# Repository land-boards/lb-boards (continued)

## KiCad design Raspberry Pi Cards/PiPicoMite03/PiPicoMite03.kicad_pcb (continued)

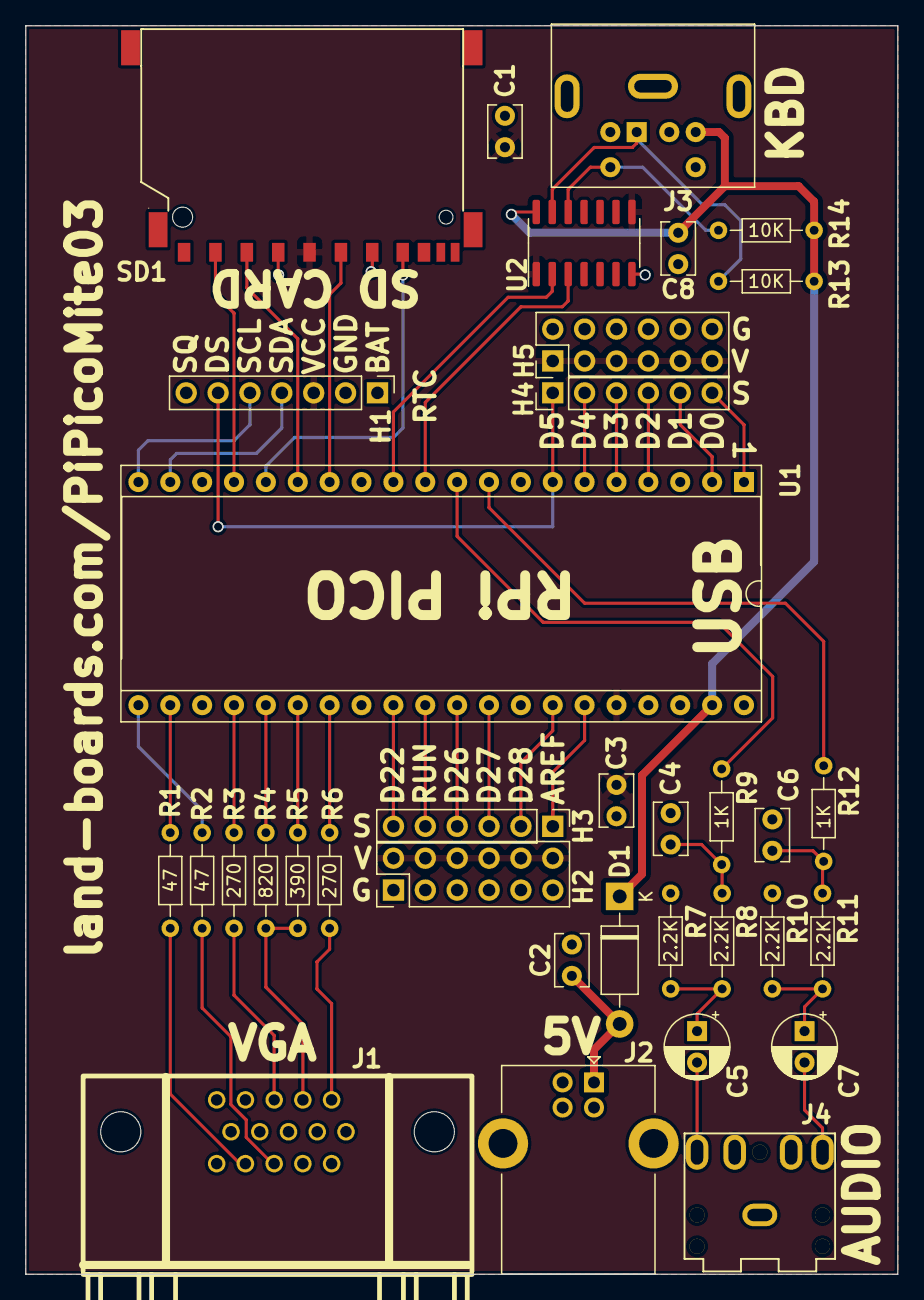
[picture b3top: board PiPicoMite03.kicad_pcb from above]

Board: 2 copper layers, 69.5 x 99.5 mm, 36 parts (0 on the bottom side), 45 nets.

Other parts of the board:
TEST: COUPON; TEST_BLK-REAR

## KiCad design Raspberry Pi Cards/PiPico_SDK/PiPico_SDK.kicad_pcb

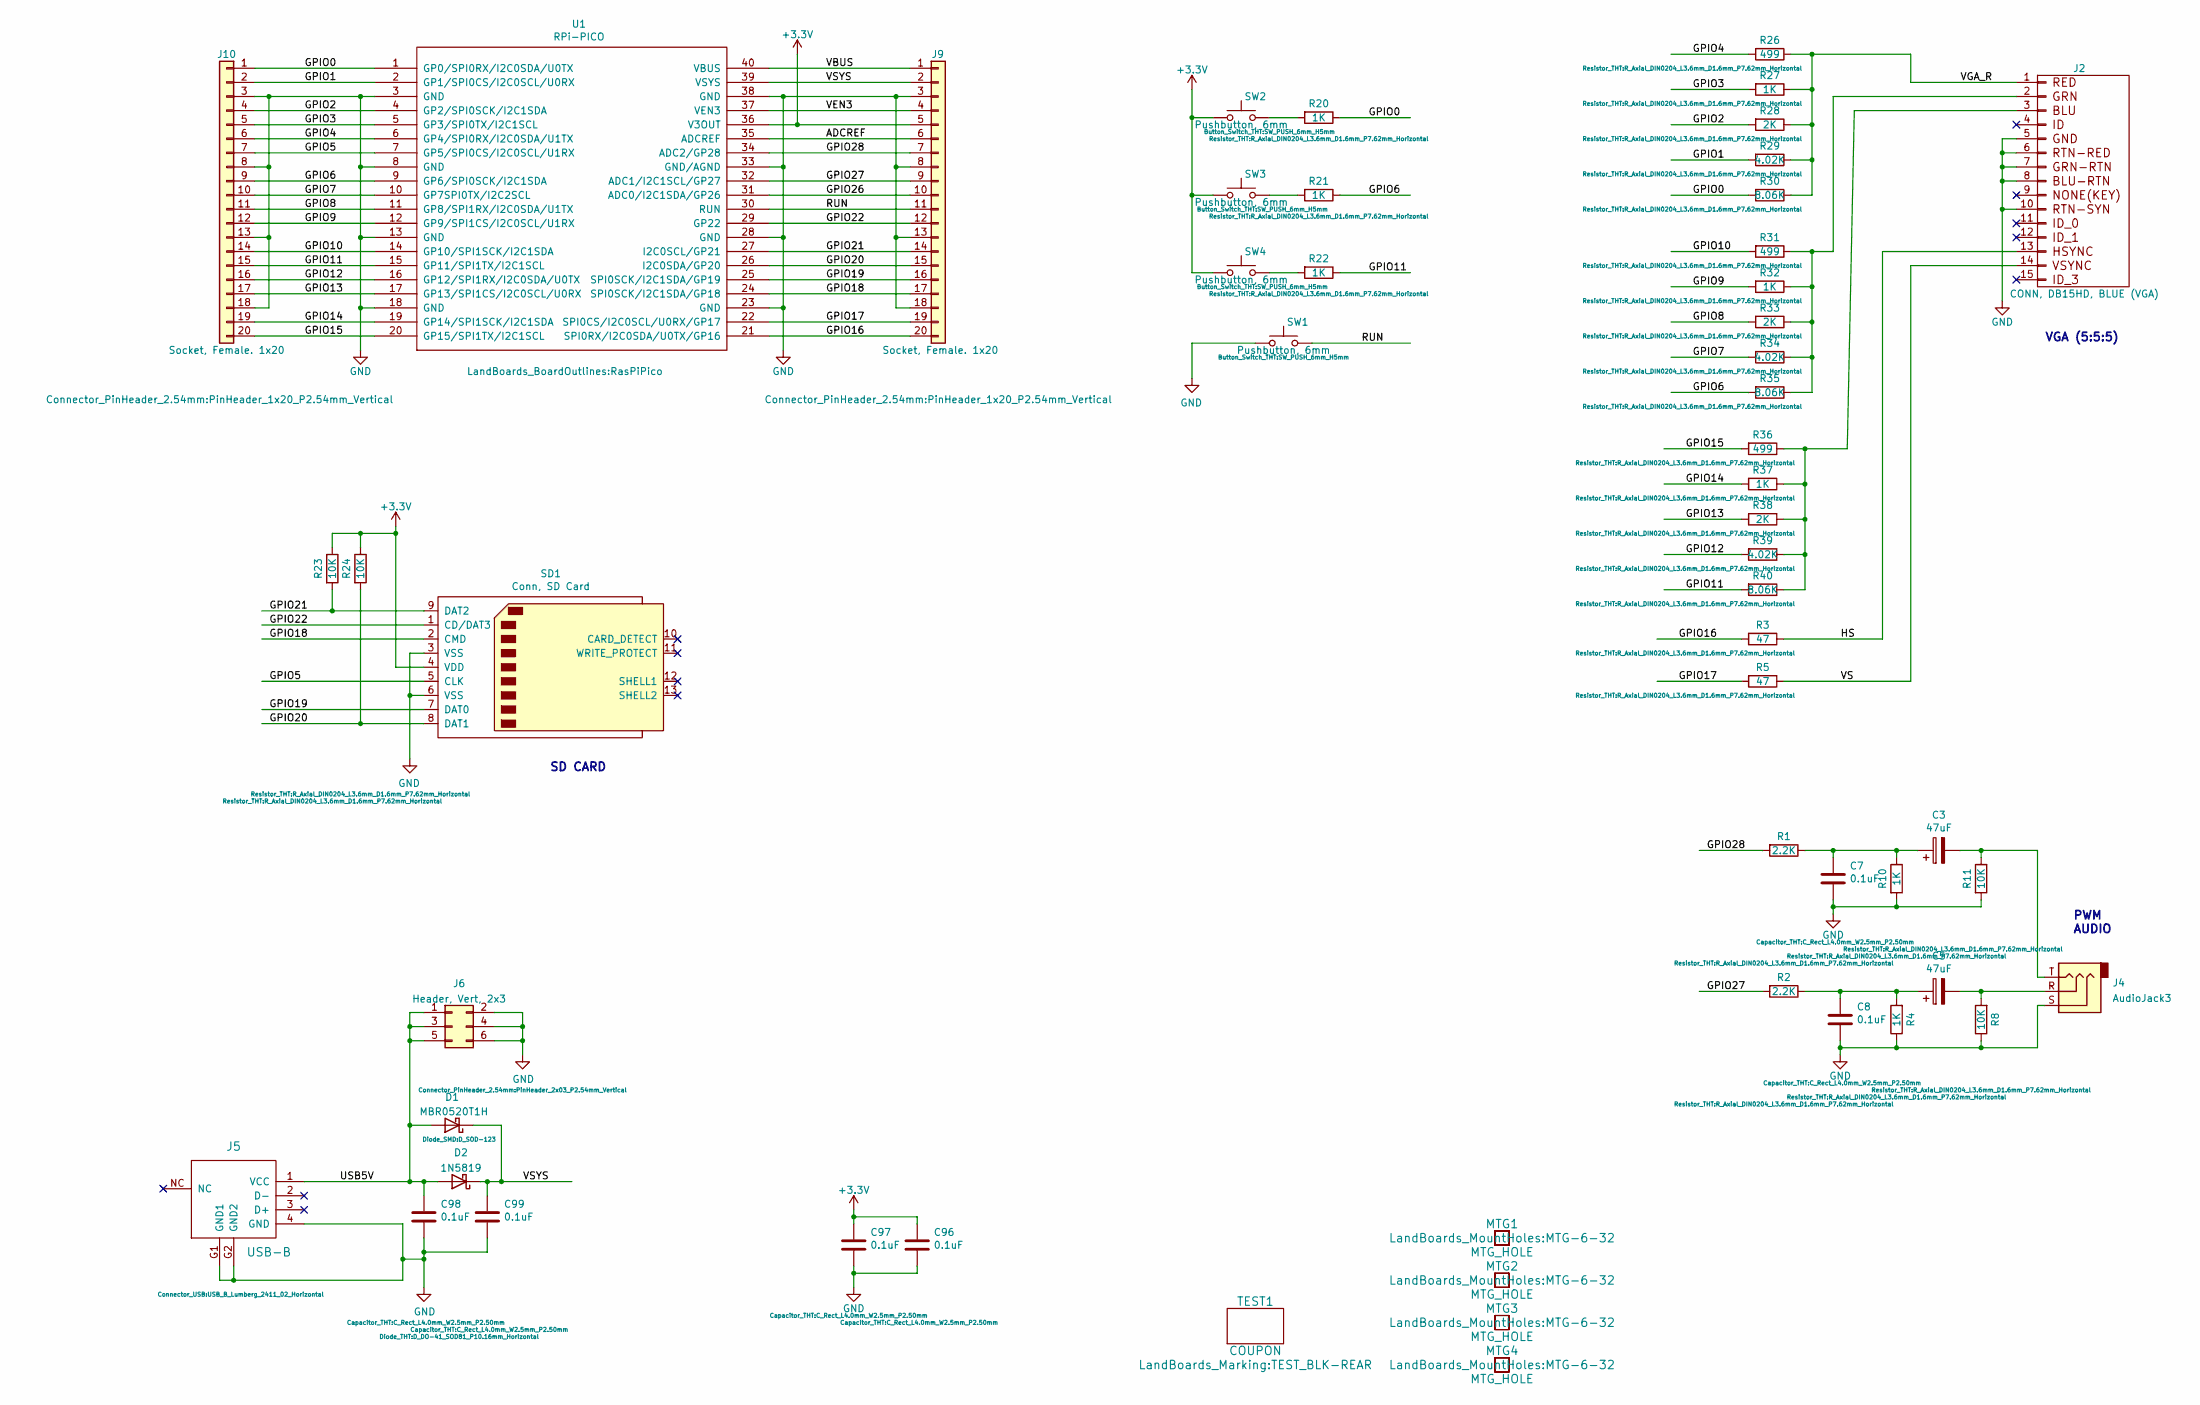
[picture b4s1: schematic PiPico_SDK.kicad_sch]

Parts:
C3, C5: 47uF; CP_Radial_D5.0mm_P2.50mm
C7, C8, C96, C97, C98, C99: 0.1uF; C_Rect_L4.0mm_W2.5mm_P2.50mm
D1: MBR0520T1H; D_SOD-123
D2: 1N5819; D_DO-41_SOD81_P10.16mm_Horizontal
J2: CONN, DB15HD, BLUE (VGA); DB_15F-VGA-fixed
J4: AudioJack3; Jack_3.5mm_CUI_SJ1-3523N_Horizontal
J5: USB-B; USB_B_Lumberg_2411_02_Horizontal
J6: Header, Vert, 2x3; PinHeader_2x03_P2.54mm_Vertical
J9, J10: Socket, Female. 1x20; PinHeader_1x20_P2.54mm_Vertical
MTG1, MTG2, MTG3, MTG4: MTG_HOLE; MTG-6-32
R1, R2: 2.2K; R_Axial_DIN0204_L3.6mm_D1.6mm_P7.62mm_Horizontal
R3, R5: 47; R_Axial_DIN0204_L3.6mm_D1.6mm_P7.62mm_Horizontal
R4, R10, R20, R21, R22, R27, R32, R37: 1K; R_Axial_DIN0204_L3.6mm_D1.6mm_P7.62mm_Horizontal
R8, R11, R23, R24: 10K; R_Axial_DIN0204_L3.6mm_D1.6mm_P7.62mm_Horizontal
R26, R31, R36: 499; R_Axial_DIN0204_L3.6mm_D1.6mm_P7.62mm_Horizontal
R28, R33, R38: 2K; R_Axial_DIN0204_L3.6mm_D1.6mm_P7.62mm_Horizontal
R29, R34, R39: 4.02K; R_Axial_DIN0204_L3.6mm_D1.6mm_P7.62mm_Horizontal
R30, R35, R40: 8.06K; R_Axial_DIN0204_L3.6mm_D1.6mm_P7.62mm_Horizontal
SD1: Conn, SD Card; SD_CARD
SW1, SW2, SW3, SW4: Pushbutton, 6mm; SW_PUSH_6mm_H5mm
TEST1: COUPON; TEST_BLK-REAR
U1: RPi-PICO; RasPiPico

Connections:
+3V3: C96.1, C97.1, J9.5, R23.1, R24.1, SD1.4 (VDD), SW2.1, SW3.1, SW4.1, U1.36 (V3OUT)
/ADCREF: J9.6, U1.35 (ADCREF)
/GPIO0: J10.1, R20.1, R30.2, U1.1 (GP0/SPI0RX/I2C0SDA/U0TX)
/GPIO1: J10.2, R29.2, U1.2 (GP1/SPI0CS/I2C0SCL/U0RX)
/GPIO2: J10.4, R28.2, U1.4 (GP2/SPI0SCK/I2C1SDA)
/GPIO3: J10.5, R27.2, U1.5 (GP3/SPI0TX/I2C1SCL)
/GPIO4: J10.6, R26.2, U1.6 (GP4/SPI0RX/I2C0SDA/U1TX)
/GPIO5: J10.7, SD1.5 (CLK), U1.7 (GP5/SPI0CS/I2C0SCL/U1RX)
/GPIO6: J10.9, R21.1, R35.2, U1.9 (GP6/SPI0SCK/I2C1SDA)
/GPIO7: J10.10, R34.2, U1.10 (GP7SPI0TX/I2C2SCL)
/GPIO8: J10.11, R33.2, U1.11 (GP8/SPI1RX/I2C0SDA/U1TX)
/GPIO9: J10.12, R32.2, U1.12 (GP9/SPI1CS/I2C0SCL/U1RX)
/GPIO10: J10.14, R31.2, U1.14 (GP10/SPI1SCK/I2C1SDA)
/GPIO11: J10.15, R22.1, R40.2, U1.15 (GP11/SPI1TX/I2C1SCL)
/GPIO12: J10.16, R39.2, U1.16 (GP12/SPI1RX/I2C0SDA/U0TX)
/GPIO13: J10.17, R38.2, U1.17 (GP13/SPI1CS/I2C0SCL/U0RX)
/GPIO14: J10.19, R37.2, U1.19 (GP14/SPI1SCK/I2C1SDA)
/GPIO15: J10.20, R36.2, U1.20 (GP15/SPI1TX/I2C1SCL)
/GPIO16: J9.20, R3.2, U1.21 (SPI0RX/I2C0SDA/U0TX/GP16)
/GPIO17: J9.19, R5.2, U1.22 (SPI0CS/I2C0SCL/U0RX/GP17)
/GPIO18: J9.17, SD1.2 (CMD), U1.24 (SPI0SCK/I2C1SDA/GP18)
/GPIO19: J9.16, SD1.7 (DAT0), U1.25 (SPI0SCK/I2C1SDA/GP19)
/GPIO20: J9.15, R24.2, SD1.8 (DAT1), U1.26 (I2C0SDA/GP20)
/GPIO21: J9.14, R23.2, SD1.9 (DAT2), U1.27 (I2C0SCL/GP21)
/GPIO22: J9.12, SD1.1 (CD/DAT3), U1.29 (GP22)
/GPIO26: J9.10, U1.31 (ADC0/I2C1SDA/GP26)
/GPIO27: J9.9, R2.2, U1.32 (ADC1/I2C1SCL/GP27)
/GPIO28: J9.7, R1.2, U1.34 (ADC2/GP28)
/HS: J2.13, R3.1
/RUN: J9.11, SW1.2, U1.30 (RUN)
/USB5V: C98.1, D1.2 (A), D2.2 (A), J5.1 (VCC), J6.1, J6.3, J6.5
/VBUS: J9.1, U1.40 (VBUS)
/VEN3: J9.4, U1.37 (VEN3)
/VGA_R: J2.1, R26.1, R27.1, R28.1, R29.1, R30.1
/VS: J2.14, R5.1
/VSYS: C99.1, D1.1 (K), D2.1 (K), J9.2, U1.39 (VSYS)
GND: C7.2, C8.2, C96.2, C97.2, C98.2, C99.2, J2.5, J2.6, J2.7, J2.8, J2.10, J4.S, J5.4 (GND), J5.G1 (GND1), J5.G2 (GND2), J6.2, J6.4, J6.6, J9.3, J9.8, J9.13, J9.18, J10.3, J10.8, J10.13, J10.18, R4.1, R8.1, R10.2, R11.2, SD1.3 (VSS), SD1.6 (VSS), SW1.1, U1.3 (GND), U1.8 (GND), U1.13 (GND), U1.18 (GND), U1.23 (GND), U1.28 (GND), U1.33 (GND/AGND), U1.38 (GND)
unnamed: C5.1, C8.1, R2.1, R4.2
unnamed: C5.2, J4.R, R8.2
unnamed: J2.2, R31.1, R32.1, R33.1, R34.1, R35.1
unnamed: J2.3, R36.1, R37.1, R38.1, R39.1, R40.1
unnamed: C3.2, J4.T, R11.1
unnamed: C3.1, C7.1, R1.1, R10.1
unnamed: R22.2, SW4.2
unnamed: R20.2, SW2.2
unnamed: R21.2, SW3.2

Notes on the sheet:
PWM AUDIO
VGA (5:5:5)
SD CARD

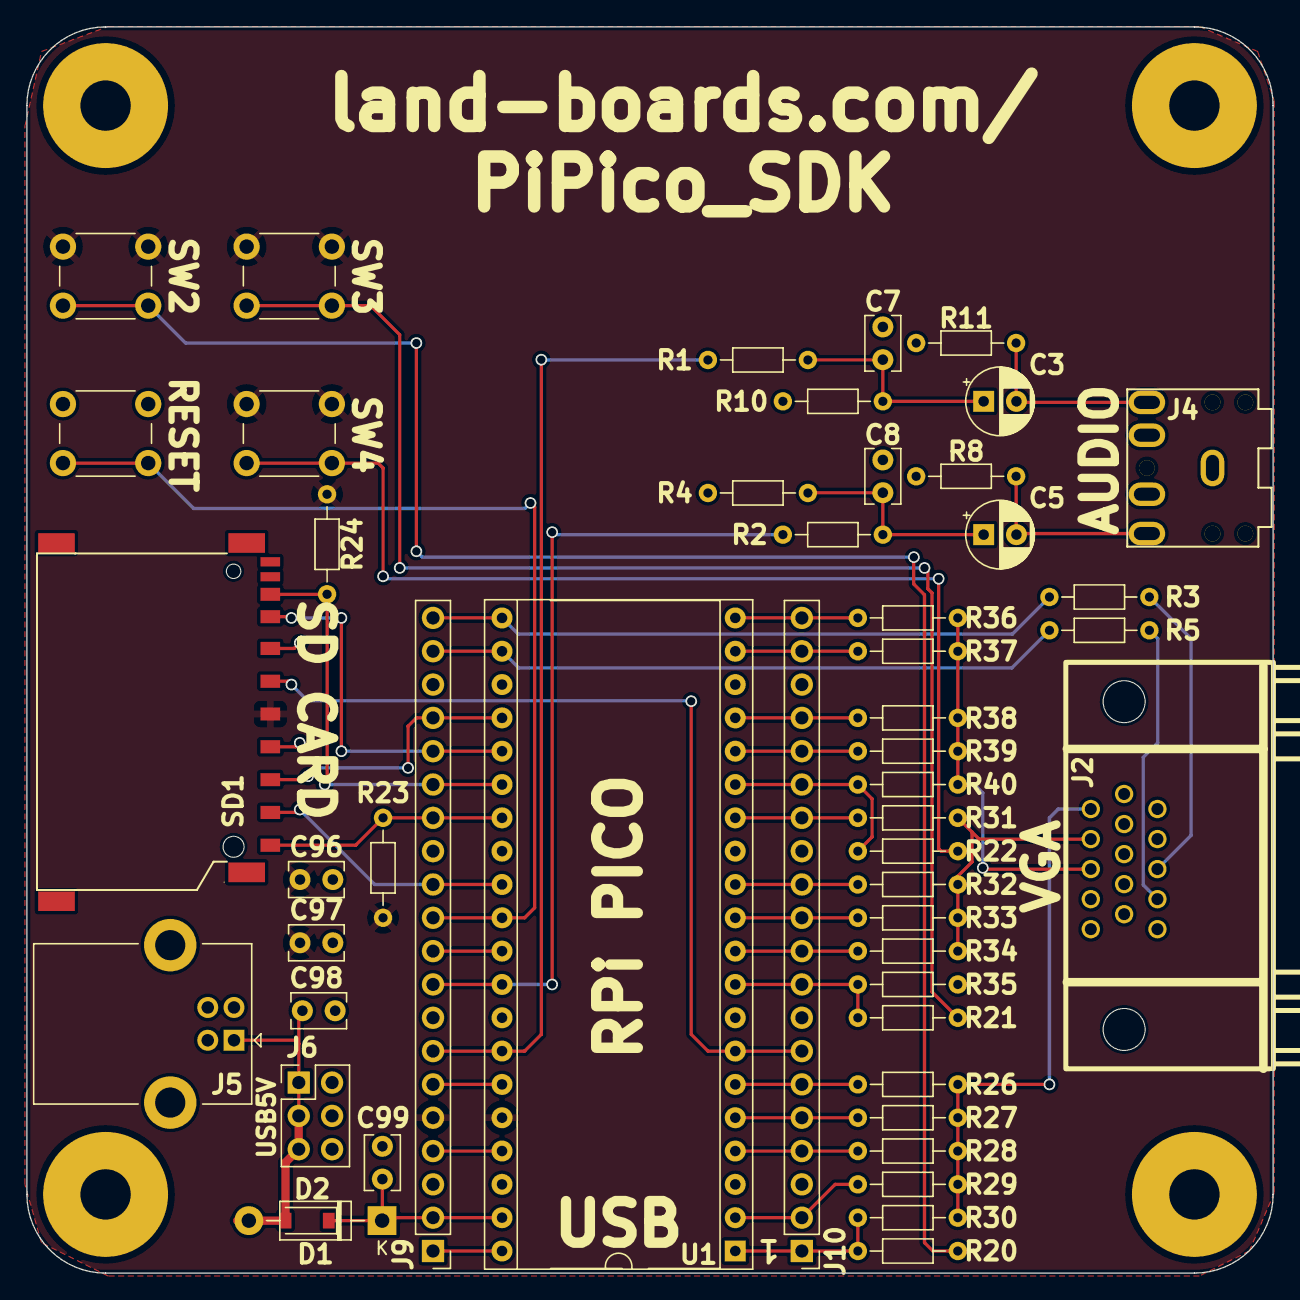
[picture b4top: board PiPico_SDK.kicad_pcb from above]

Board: 2 copper layers, 95.0 x 95.0 mm, 55 parts (0 on the bottom side), 46 nets.

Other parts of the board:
TEST: COUPON; TEST_BLK-REAR

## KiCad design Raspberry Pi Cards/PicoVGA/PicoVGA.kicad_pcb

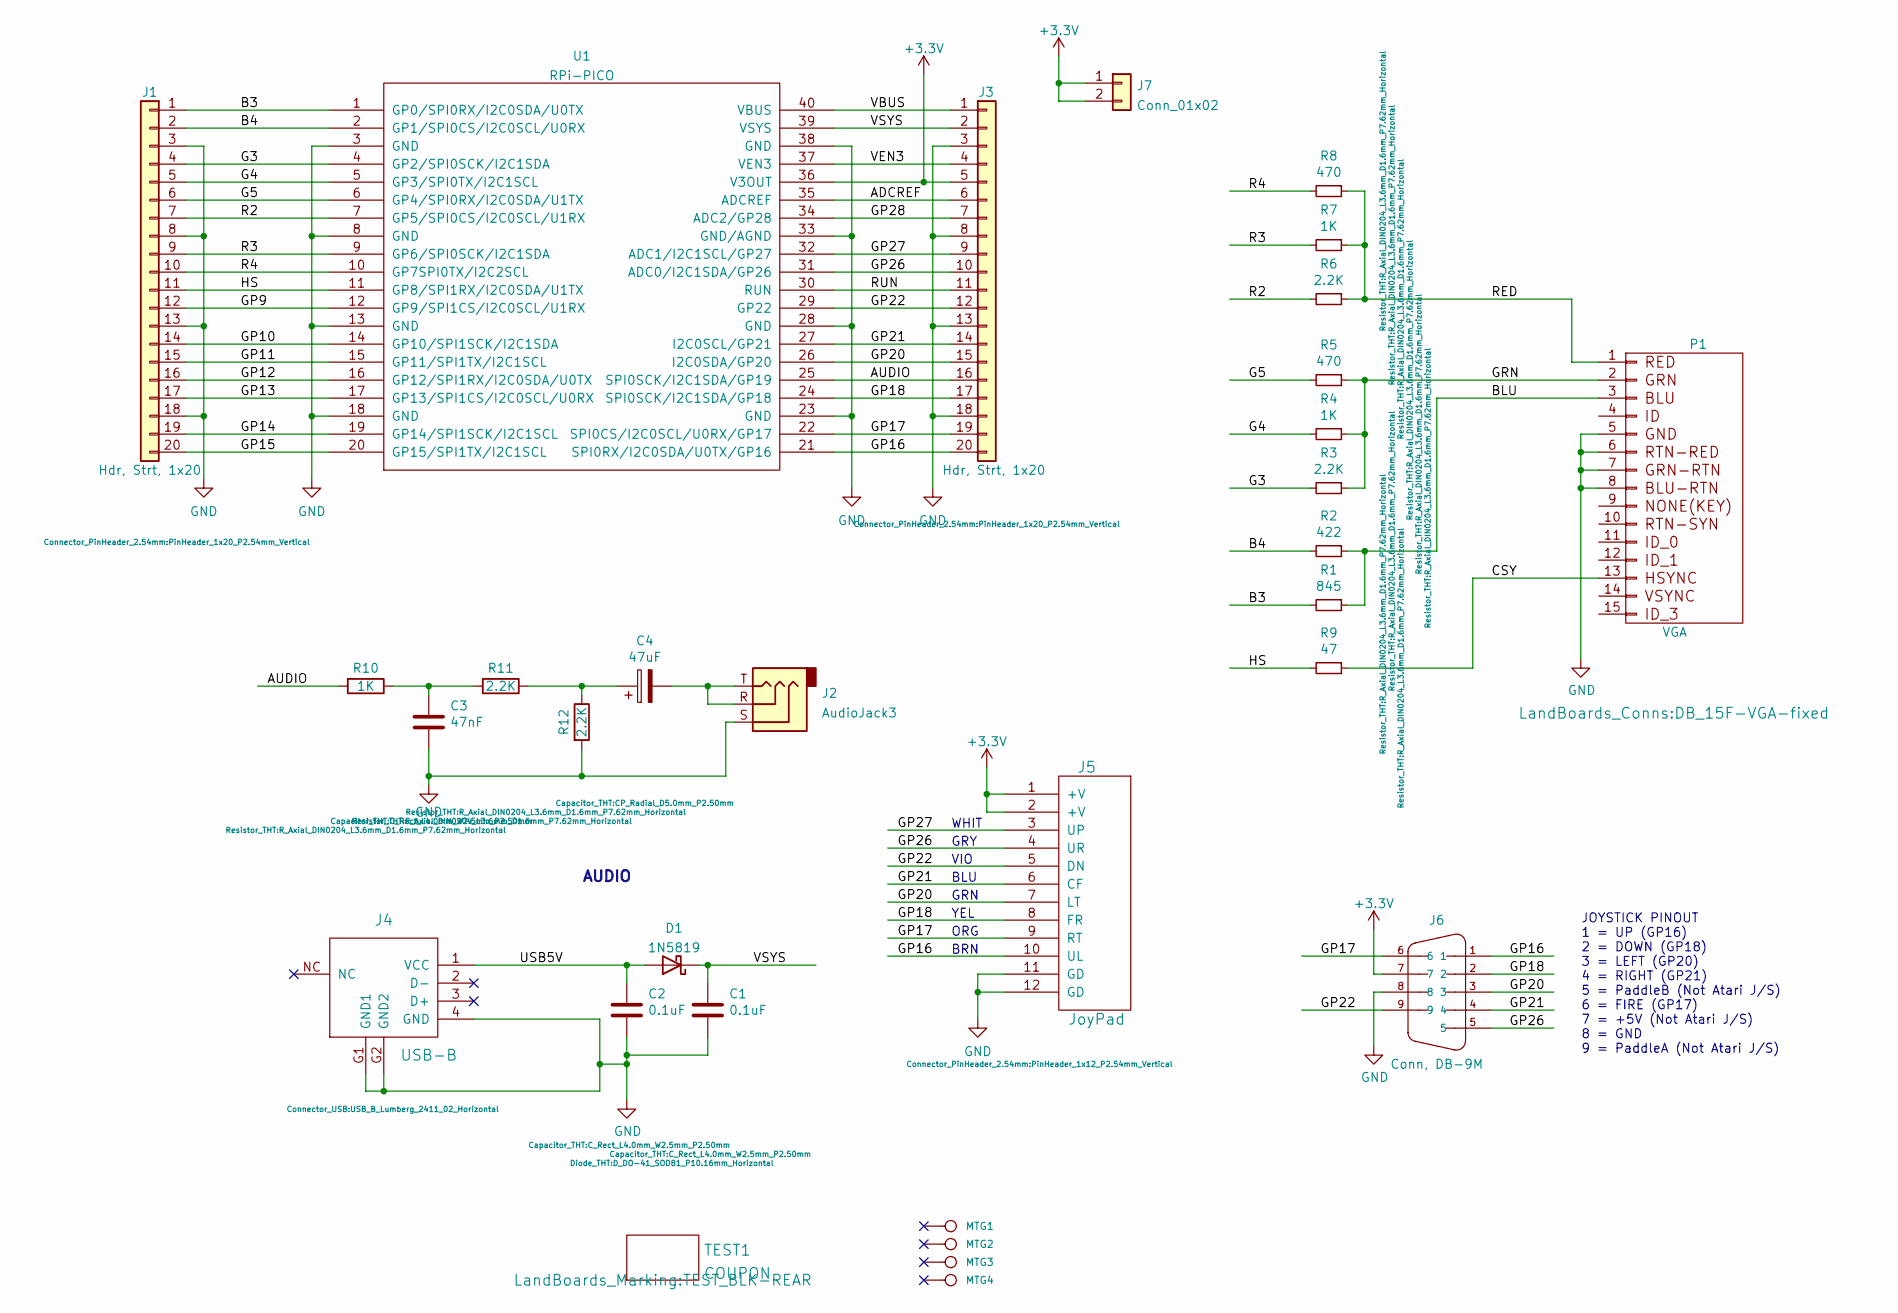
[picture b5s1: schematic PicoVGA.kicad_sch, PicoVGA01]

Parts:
C1, C2: 0.1uF; C_Rect_L4.0mm_W2.5mm_P2.50mm
C3: 47nF; C_Rect_L4.0mm_W2.5mm_P2.50mm
C4: 47uF; CP_Radial_D5.0mm_P2.50mm
D1: 1N5819; D_DO-41_SOD81_P10.16mm_Horizontal
J1, J3: Hdr, Strt, 1x20; PinHeader_1x20_P2.54mm_Vertical
J2: AudioJack3; Jack_3.5mm_CUI_SJ1-3523N_Horizontal
J4: USB-B; USB_B_Lumberg_2411_02_Horizontal
J5: JoyPad; PinHeader_1x12_P2.54mm_Vertical
J6: Conn, DB-9M; DSUB-9_Male_Horizontal_P2.77x2.84mm_EdgePinOffset4.94mm_Hou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
J7: Conn_01x02; PinHeader_1x02_P2.54mm_Vertical
MTG1, MTG2, MTG3, MTG4: CONN_1; MTG-4-40
P1: VGA; DB_15F-VGA-fixed
R1: 845; R_Axial_DIN0204_L3.6mm_D1.6mm_P7.62mm_Horizontal
R2: 422; R_Axial_DIN0204_L3.6mm_D1.6mm_P7.62mm_Horizontal
R3, R6, R11, R12: 2.2K; R_Axial_DIN0204_L3.6mm_D1.6mm_P7.62mm_Horizontal
R4, R7, R10: 1K; R_Axial_DIN0204_L3.6mm_D1.6mm_P7.62mm_Horizontal
R5, R8: 470; R_Axial_DIN0204_L3.6mm_D1.6mm_P7.62mm_Horizontal
R9: 47; R_Axial_DIN0204_L3.6mm_D1.6mm_P7.62mm_Horizontal
TEST1: COUPON; TEST_BLK-REAR
U1: RPi-PICO; RasPiPico

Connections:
+3V3: J3.5, J5.1 (+V), J5.2 (+V), J6.7, J7.1, J7.2, U1.36 (V3OUT)
/ADCREF: J3.6, U1.35 (ADCREF)
/AUDIO: J3.16, R10.2, U1.25 (SPI0SCK/I2C1SDA/GP19)
/B3: J1.1, R1.2, U1.1 (GP0/SPI0RX/I2C0SDA/U0TX)
/B4: J1.2, R2.2, U1.2 (GP1/SPI0CS/I2C0SCL/U0RX)
/BLU: P1.3, R1.1, R2.1
/CSY: P1.13, R9.1
/G3: J1.4, R3.2, U1.4 (GP2/SPI0SCK/I2C1SDA)
/G4: J1.5, R4.2, U1.5 (GP3/SPI0TX/I2C1SCL)
/G5: J1.6, R5.2, U1.6 (GP4/SPI0RX/I2C0SDA/U1TX)
/GP9: J1.12, U1.12 (GP9/SPI1CS/I2C0SCL/U1RX)
/GP10: J1.14, U1.14 (GP10/SPI1SCK/I2C1SDA)
/GP11: J1.15, U1.15 (GP11/SPI1TX/I2C1SCL)
/GP12: J1.16, U1.16 (GP12/SPI1RX/I2C0SDA/U0TX)
/GP13: J1.17, U1.17 (GP13/SPI1CS/I2C0SCL/U0RX)
/GP14: J1.19, U1.19 (GP14/SPI1SCK/I2C1SCL)
/GP15: J1.20, U1.20 (GP15/SPI1TX/I2C1SCL)
/GP16: J3.20, J5.10 (UL), J6.1, U1.21 (SPI0RX/I2C0SDA/U0TX/GP16)
/GP17: J3.19, J5.9 (RT), J6.6, U1.22 (SPI0CS/I2C0SCL/U0RX/GP17)
/GP18: J3.17, J5.8 (FR), J6.2, U1.24 (SPI0SCK/I2C1SDA/GP18)
/GP20: J3.15, J5.7 (LT), J6.3, U1.26 (I2C0SDA/GP20)
/GP21: J3.14, J5.6 (CF), J6.4, U1.27 (I2C0SCL/GP21)
/GP22: J3.12, J5.5 (DN), J6.9, U1.29 (GP22)
/GP26: J3.10, J5.4 (UR), J6.5, U1.31 (ADC0/I2C1SDA/GP26)
/GP27: J3.9, J5.3 (UP), U1.32 (ADC1/I2C1SCL/GP27)
/GP28: J3.7, U1.34 (ADC2/GP28)
/GRN: P1.2, R3.1, R4.1, R5.1
/HS: J1.11, R9.2, U1.11 (GP8/SPI1RX/I2C0SDA/U1TX)
/R2: J1.7, R6.2, U1.7 (GP5/SPI0CS/I2C0SCL/U1RX)
/R3: J1.9, R7.2, U1.9 (GP6/SPI0SCK/I2C1SDA)
/R4: J1.10, R8.2, U1.10 (GP7SPI0TX/I2C2SCL)
/RED: P1.1, R6.1, R7.1, R8.1
/RUN: J3.11, U1.30 (RUN)
/USB5V: C2.1, D1.2 (A), J4.1 (VCC)
/VBUS: J3.1, U1.40 (VBUS)
/VEN3: J3.4, U1.37 (VEN3)
/VSYS: C1.1, D1.1 (K), J3.2, U1.39 (VSYS)
GND: C1.2, C2.2, C3.2, J1.3, J1.8, J1.13, J1.18, J2.S, J3.3, J3.8, J3.13, J3.18, J4.4 (GND), J4.G1 (GND1), J4.G2 (GND2), J5.11 (GD), J5.12 (GD), J6.8, P1.5, P1.6, P1.7, P1.8, R12.2, U1.3 (GND), U1.8 (GND), U1.13 (GND), U1.18 (GND), U1.23 (GND), U1.28 (GND), U1.33 (GND/AGND), U1.38 (GND)
unnamed: C3.1, R10.1, R11.2
unnamed: C4.1, R11.1, R12.1
unnamed: C4.2, J2.R, J2.T

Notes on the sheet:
GRY
GRN
ORG
JOYSTICK PINOUT 1 = UP (GP16) 2 = DOWN (GP18) 3 = LEFT (GP20) 4 = RIGHT (GP21) 5 = PaddleB (Not Atari J/S) 6 = FIRE (GP17) 7 = +5V (Not Atari J/S) 8 = GND 9 = PaddleA (Not Atari J/S)
BRN
WHIT
YEL
BLU
VIO
AUDIO

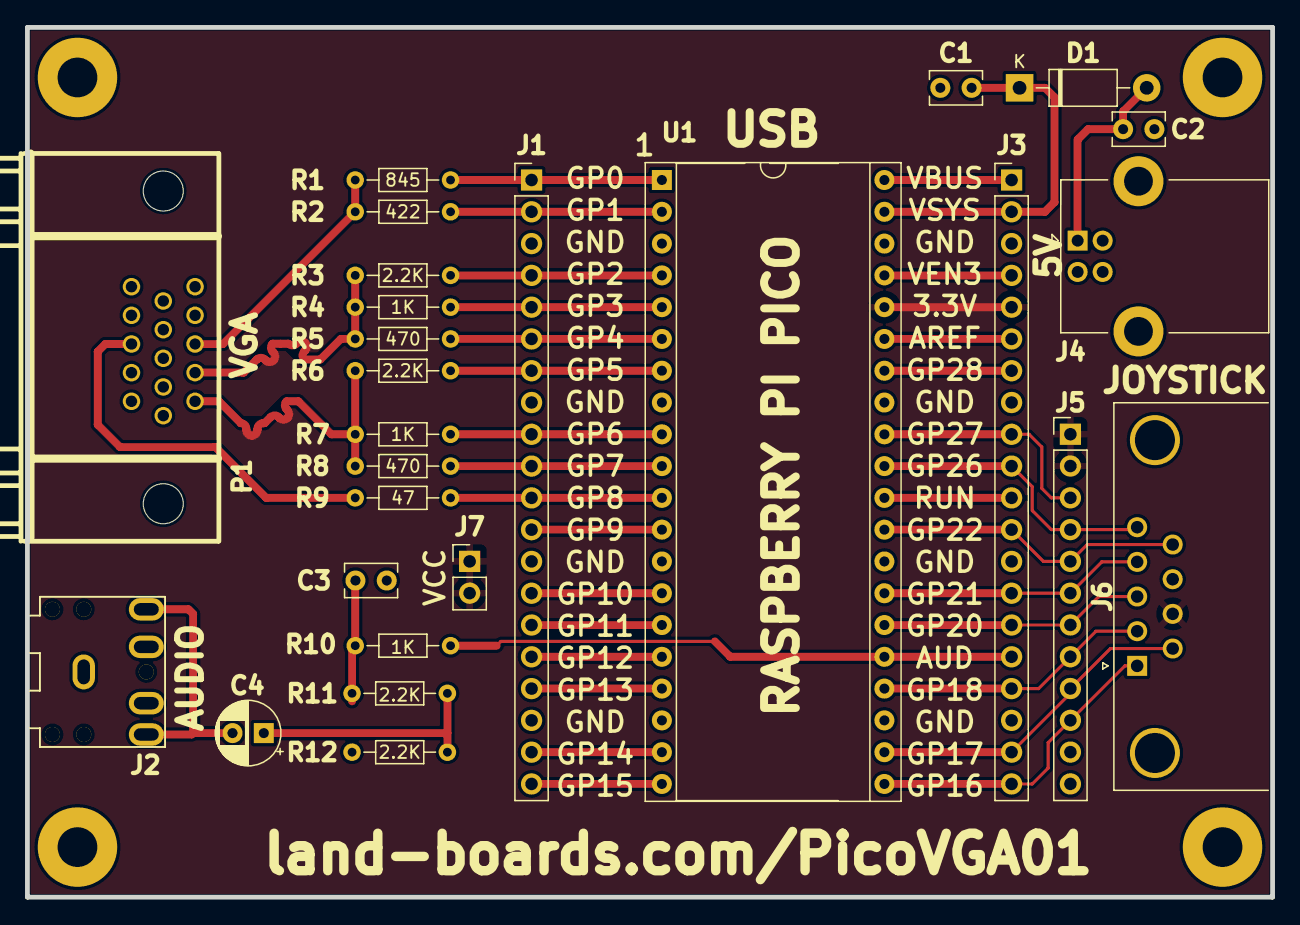
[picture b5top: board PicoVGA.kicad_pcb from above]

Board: 2 copper layers, 99.5 x 69.5 mm, 31 parts (0 on the bottom side), 41 nets.

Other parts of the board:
TEST: COUPON; TEST_BLK-REAR

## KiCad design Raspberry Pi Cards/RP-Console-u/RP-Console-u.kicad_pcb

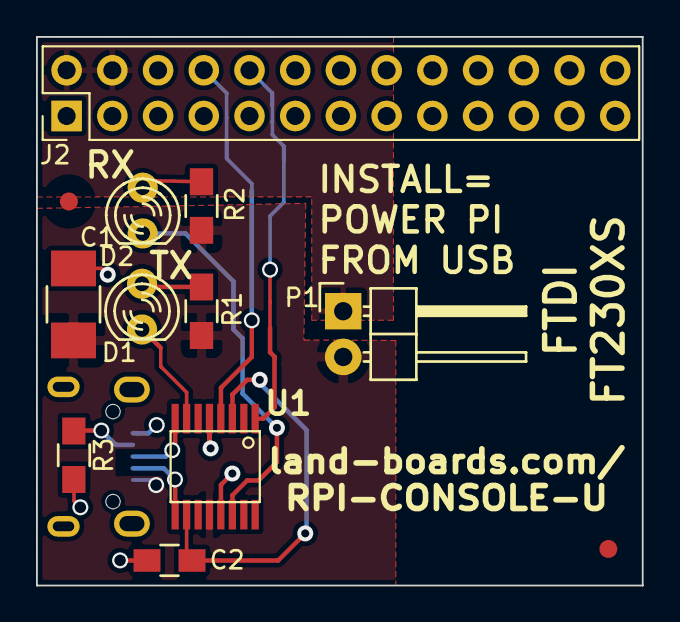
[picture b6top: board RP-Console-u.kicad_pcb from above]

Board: 2 copper layers, 33.7 x 30.5 mm, 13 parts (1 on the bottom side), 13 nets.

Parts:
C1: 10uF; C_1210_HandSoldering
C2: 0.1uF; C_0805_HandSoldering
D1, D2: LED; LED-3MM
FID1, FID2: CONN_1; FIDUCIAL
J1: USB-MICRO-B; USB_Micro-B_Wuerth_629105150521
J2: RASPIO; PinHeader_2x13_P2.54mm_Vertical
P1: CONN_2; Pin_Header_Angled_1x02
R1, R2: 270; R_0805_HandSoldering
R3: DNP; R_0805_HandSoldering
U1: FT230XS; ssop-16

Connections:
/+3.3V-USB: C2.1, U1.3, U1.10
/+5V: J2.2, J2.4, P1.1
/+5V-USB: C1.1, J1.1, P1.2, R1.1, R2.1, U1.12
/DM: J1.2, U1.9
/DP: J1.3, U1.8
/GND: C1.2, C2.2, J1.5, J1.6, J2.6, J2.9, J2.14, J2.20, J2.25, R3.2, U1.5, U1.13
/PI2USB: J2.8, U1.4
/PUP0: D1.1, R1.2
/PUP1: D2.1, R2.2
/RXLED*: D2.2, U1.14
/TXLED*: D1.2, U1.7
/USB2PI: J2.10, U1.1
unnamed: J1.4, R3.1
